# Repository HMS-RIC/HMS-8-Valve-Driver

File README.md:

# HMS 8-Channel Valve Driver

A circuit for driving up to 8 small valves.

The board takes 8 channels of digital inputs (3.3V or 5V) and can drive valves at up to 50V and 500mA. Inputs can be connected via BNC connectors (channels 1–4) or a 0.1" header (all 8 channels). Optional push buttons on channels 1–4 allow for manual valve activation (e.g., to flush or clean the valve lines).

## Fabrication and Assembly

1) Order a batch of printed circuit boards (PCBs) using the provided Gerber files. 
	- You can upload the [Gerber .zip file](Gerbers/HMS-8-Channel-Valve-Driver-v1.3-Gerbers.zip?raw=true) to a online PCB fabricator, like [OSH Park](https://oshpark.com/) or [DK Red](https://www.digikey.com/en/pcb-builder/?p=dkred) and use the default settings for a 2-layer board.

2) Order the components listed in the Bill of Materials, and solder them into the PCB as shown in the photo above.

**Notes**
- Make sure to place the transistor array chip (ULQ2803A) in the correct orientation (the notch on the chip should line up with the silkscreen).
- Input connectors (BNC or 1x10 header) are optional depending on how you plan to use the board and how many channels you'll need.
- Similarly, manual valve control buttons are optional.

#### Output connectors
You have several choices for the output connectors to the valves since the holes in the board have standard 0.1" spacing. Two options are shown in the images below:
- A simple 0.1" rectangular socket (or header). Some valves can just plug right in (like the Lee LHD series show in the photo).
- A 0.1" screw terminal. Makes it easier to connect directly to wires.

## Usage

1) Plug in a "wall-wart" power supply with the correct voltage for your valves (likely 5V, 12V, or 24V). Make sure the power supply can provide enough current for all the valves you plan to use (or at least as many valves as might be on at once).

2) Connect valves to the output connectors. NOTE: Make sure the valves draw 500mA or less.

3) Provide digital signals to the valve input lines. These may be 3.3V or 5V signals, and might come from a device like an Arduino or a DAQ (data acquisition) board. Make sure that the valve driver and the signal generating device share a common ground connection, either through the BNC shield, or the GND pin on the input header. The circuit will energize the valves in response to a HIGH (3–5V) input signal.

4) If needed, you can also use the buttons to manually energize the valves.

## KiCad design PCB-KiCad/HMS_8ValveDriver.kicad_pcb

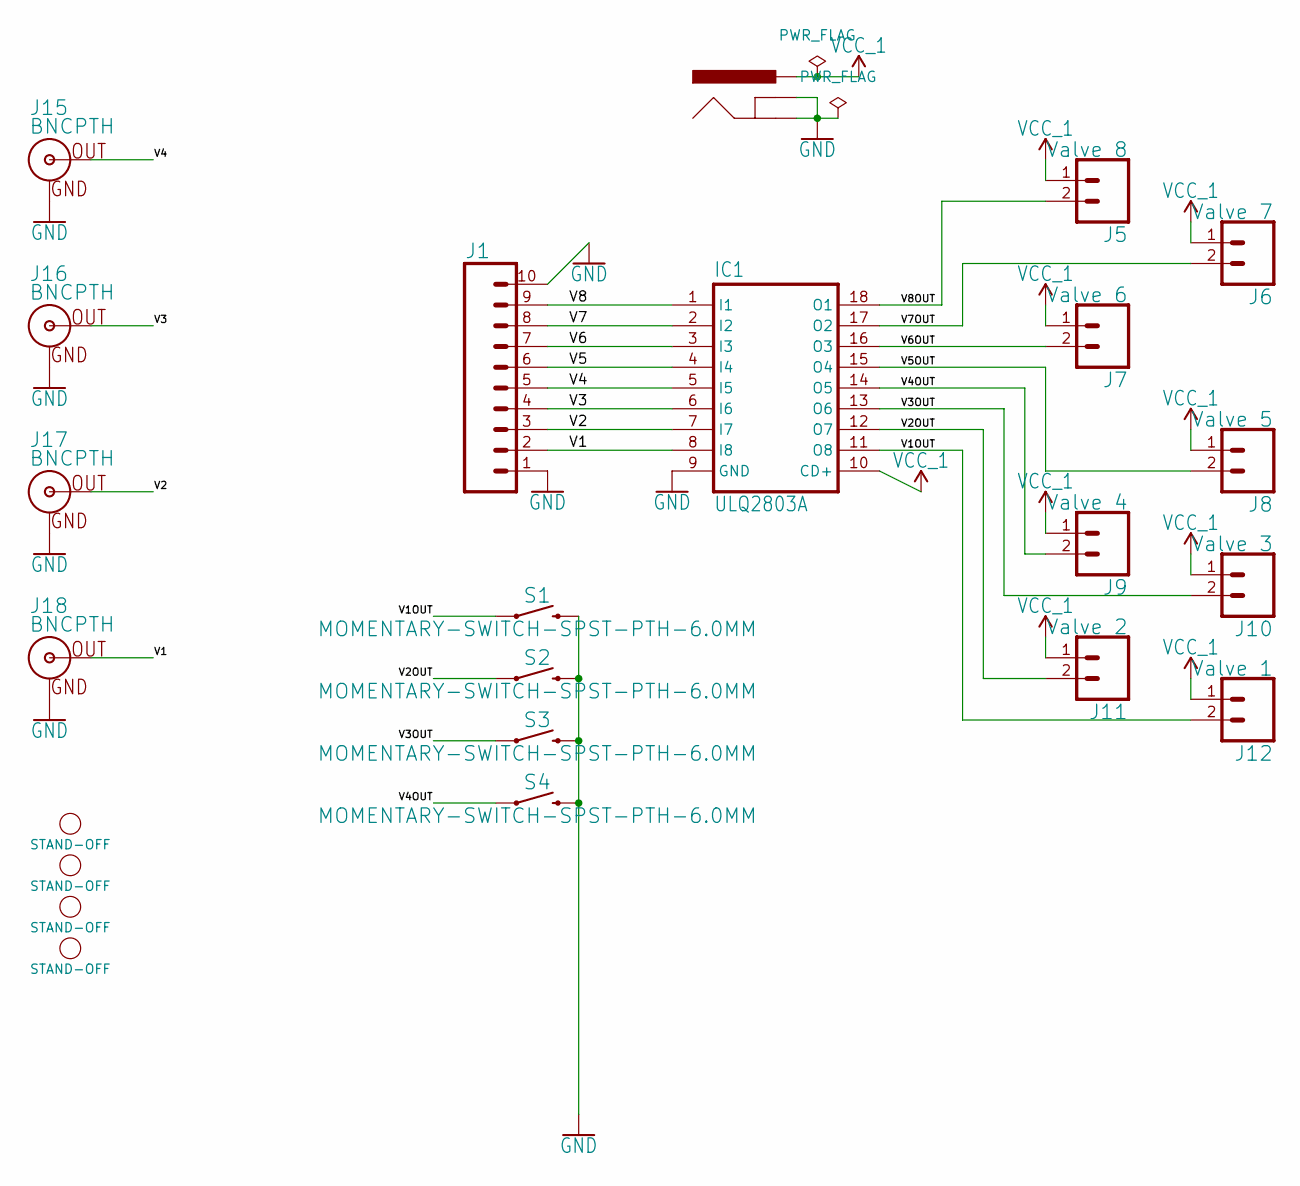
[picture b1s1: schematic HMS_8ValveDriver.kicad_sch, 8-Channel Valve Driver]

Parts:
H1, H2, H3, H4: STAND-OFF
IC1: ULQ2803A; DIL18
J1: CONN_10"; 1X10
J4: POWER_JACK; POWER_JACK_PTH
J5: Valve 8; 1X02
J6: Valve 7; 1X02
J7: Valve 6; 1X02
J8: Valve 5; 1X02
J9: Valve 4; 1X02
J10: Valve 3; 1X02
J11: Valve 2; 1X02
J12: Valve 1; 1X02
J15, J16, J17, J18: BNCPTH; BNC
S1, S2, S3, S4: MOMENTARY-SWITCH-SPST-PTH-6.0MM; TACTILE_SWITCH_PTH_6.0MM

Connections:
/V1: IC1.8 (I8), J1.2, J18.S (OUT)
/V1OUT: IC1.11 (O8), J12.2, S1.1
/V2: IC1.7 (I7), J1.3, J17.S (OUT)
/V2OUT: IC1.12 (O7), J11.2, S2.1
/V3: IC1.6 (I6), J1.4, J16.S (OUT)
/V3OUT: IC1.13 (O6), J10.2, S3.1
/V4: IC1.5 (I5), J1.5, J15.S (OUT)
/V4OUT: IC1.14 (O5), J9.2, S4.1
/V5: IC1.4 (I4), J1.6
/V5OUT: IC1.15 (O4), J8.2
/V6: IC1.3 (I3), J1.7
/V6OUT: IC1.16 (O3), J7.2
/V7: IC1.2 (I2), J1.8
/V7OUT: IC1.17 (O2), J6.2
/V8: IC1.1 (I1), J1.9
/V8OUT: IC1.18 (O1), J5.2
GND: IC1.9 (GND), J1.1, J1.10, J4.GND, J4.GNDBREAK, J15.GND, J16.GND, J17.GND, J18.GND, S1.3 (2), S2.3 (2), S3.3 (2), S4.3 (2)
VCC_1: IC1.10 (CD+), J4.PWR, J5.1, J6.1, J7.1, J8.1, J9.1, J10.1, J11.1, J12.1

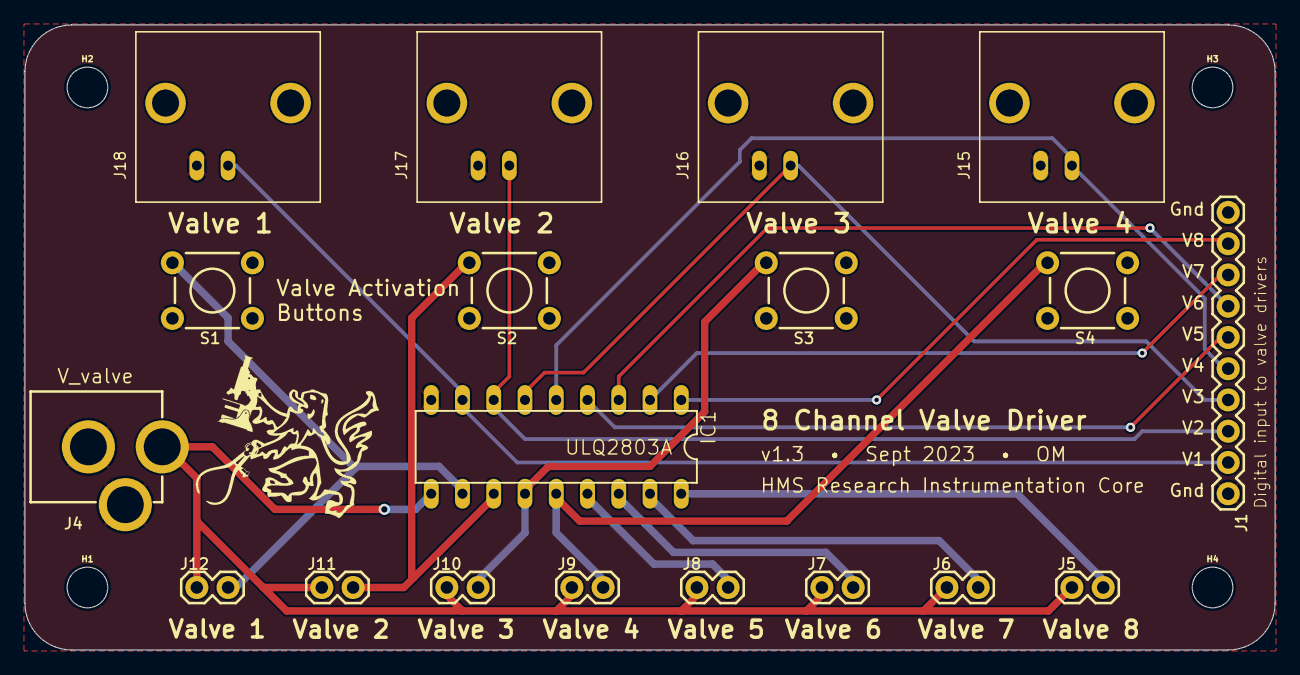
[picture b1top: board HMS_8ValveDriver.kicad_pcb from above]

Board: 2 copper layers, 101.6 x 50.8 mm, 24 parts (0 on the bottom side), 18 nets.

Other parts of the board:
U$7: RIC_LOGO_BIG

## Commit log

2023-09-22 Create LICENSE
2023-09-22 Update Readme, add images
2023-09-22 Update image
2023-09-22 Update BOM; Generate Gerbers
2023-10-03 Remove Eagle files
2023-10-03 Filename change
